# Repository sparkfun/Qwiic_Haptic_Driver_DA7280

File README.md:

SparkFun Qwiic Haptic Driver - DA7280
========================================

<table class="table table-hover table-striped table-bordered">
  <tr align="center">
   <td></td>
   <td></td>
  </tr>
  <tr align="center">
   <td><i>SparkFun Qwiic Haptic Driver - DA7280 [<a href="https://www.sparkfun.com/products/17590">ROB-17590</a>]</i></td>
   <td><i>SparkFun Qwiic Haptic Driver Kit - DA7280 [<a href="https://www.sparkfun.com/products/18247">ROB-18247</a>]</i></td>
  </tr>
</table>

The SparkFun Qwiic Haptic Driver includes an itty-bitty, Linear Resonant Actuator (LRA) vibration motor and Dialog Semiconductor's DA7280 motor driver IC for applications that require haptic feedback. The kit is intended for applications where the vibration motor needs to be mounted separately from the board. Please be aware that you will need to manually solder the wires and motor to the board.

Control the vibration motor with the DA7280 via I<sup>2</sup>C, PWM, or a combination of three general purpose input pins. Utilizing our handy Qwiic system, no soldering is required to connect it to the rest of your system. However, we still include 0.1"-spaced PTH pads in case you prefer to use a breadboard to access the driver's I<sup>2</sup>C, power, interrupt, and general purpose input pins on the edge of the board.

This board is great for projects that require a physical indicator whenever an event is triggered. Add it to your remote control to notify you when your robot has hit a wall. Combine it with an accelerometer to remind you to correct your posture. Or use it with a distance sensor to alert you when a ninja is walking up to you at your desk.

Repository Contents
-------------------

* **/Documentation** - Data sheets, additional product information
* **/Hardware** - Eagle design files (.brd, .sch)
* **/Production** - Production panel files (.brd)

Documentation
--------------

* **[Library](https://github.com/sparkfun/DA7280_Haptic_Driver_Arduino_Library)** - Arduino library
* **[Hookup Guide](https://learn.sparkfun.com/tutorials/1461)**

Product Versions
----------------

* [ROB-17590](https://www.sparkfun.com/products/17590)

Version History
---------------

* v1.0 - Initial Release

License Information
-------------------

This product is _**open source**_! 

Please review the LICENSE.md file for license information. 

If you have any questions or concerns on licensing, please contact technical support on our [SparkFun forums](https://forum.sparkfun.com/viewforum.php?f=152).

Distributed as-is; no warranty is given.

- Your friends at SparkFun.

_<COLLABORATION CREDIT>_

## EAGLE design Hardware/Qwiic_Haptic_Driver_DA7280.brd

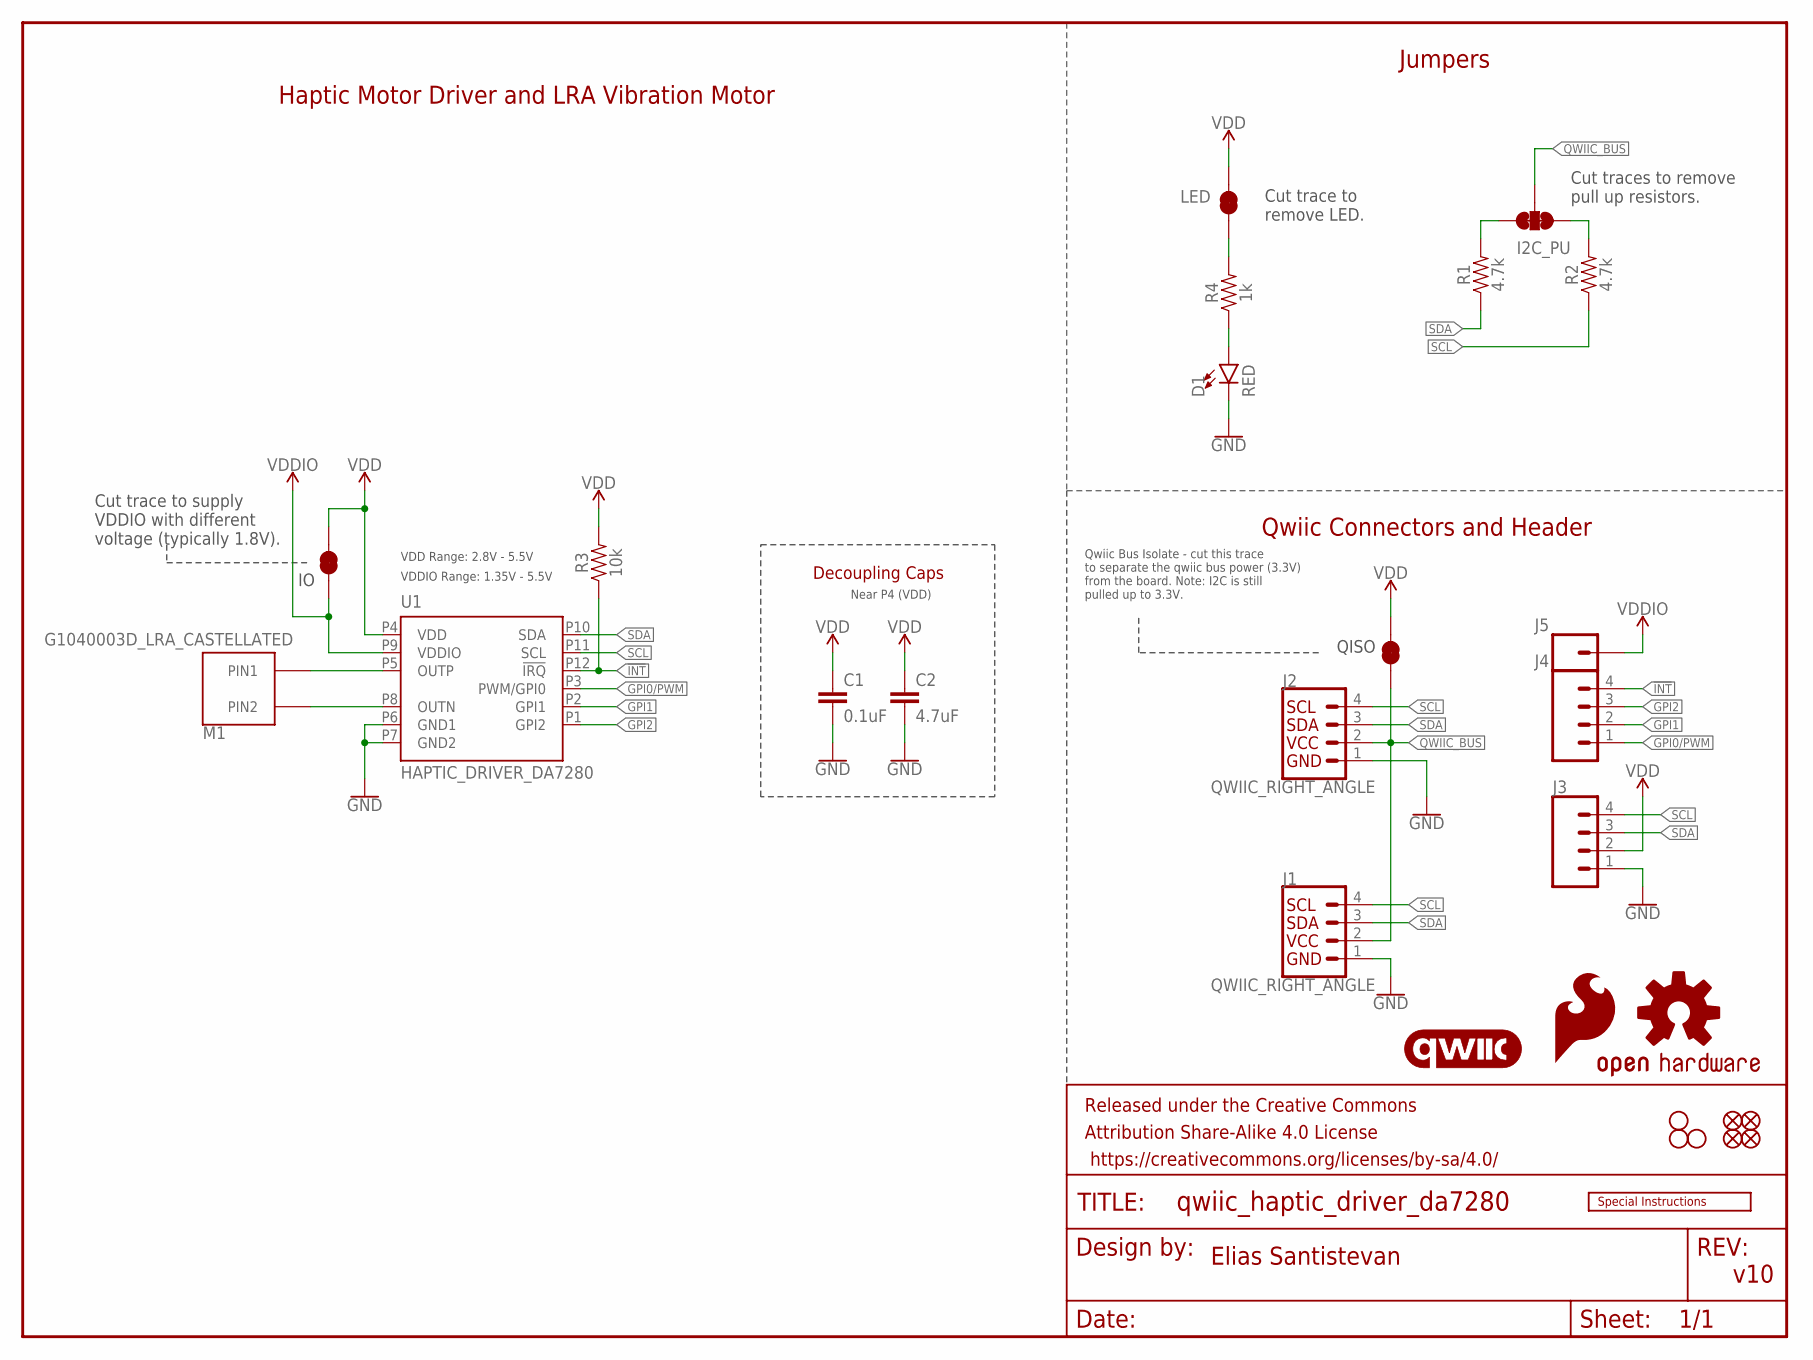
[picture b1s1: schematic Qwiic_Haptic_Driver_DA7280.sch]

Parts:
C1: 0.1uF; 0603
C2: 4.7uF; 0603
D1: RED; LED-0603
FD1, FD2, FD3, FD4: FIDUCIALUFIDUCIAL; FIDUCIAL-MICRO
FRAME1: FRAME-LETTER; CREATIVE_COMMONS
H1, H2, H4: STAND-OFFTIGHT; STAND-OFF-TIGHT
J1, J2: QWIIC_RIGHT_ANGLE; JST04_1MM_RA
J3, J4: CONN_041X04_NO_SILK_NO_POP; 1X04_NO_SILK
J5: CONN_01PTH_NO_SILK_YES_STOP; 1X01_NO_SILK
JP1, JP2, JP4: LED; SMT-JUMPER_2_NC_TRACE_SILK
JP3: I2C_PU; SMT-JUMPER_3_2-NC_TRACE_SILK
LOGO1: SPECIAL_INSTRUCTIONS-ORDERING; ORDERING_INSTRUCTIONS
LOGO2: OSHW-LOGOS; OSHW-LOGO-S
LOGO4: SFE_LOGO_FLAME.1_INCH; SFE_LOGO_FLAME_.1
M1: G1040003D_LRA_CASTELLATED; COIN_VIBRATION_MOTOR_CASTEL
R1, R2: 4.7k; 0603
R3: 10k; 0603
R4: 1k; 0603
U1: HAPTIC_DRIVER_DA7280; QFN_DA7280
U$1: QWIIC_LOGO_3MM; QWIIC_3MM

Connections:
!INT!: J4.4, R3.1, U1.P12 (!IRQ!)
GND: C1.2, C2.2, D1.C, J1.1, J2.1, J3.1, U1.P6 (GND1), U1.P7 (GND2)
GPI0/PWM: J4.1, U1.P3 (PWM/GPI0)
GPI1: J4.2, U1.P2 (GPI1)
GPI2: J4.3, U1.P1 (GPI2)
unnamed: D1.A, R4.1
unnamed: JP1.1, R4.2
unnamed: JP3.3, R1.2
unnamed: JP3.1, R2.2
unnamed: M1.P$1 (PIN1), U1.P5 (OUTP)
unnamed: M1.P$2 (PIN2), U1.P8 (OUTN)
QWIIC_BUS: J1.2, J2.2, JP3.2, JP4.1
SCL: J1.4, J2.4, J3.4, R2.1, U1.P11 (SCL)
SDA: J1.3, J2.3, J3.3, R1.1, U1.P10 (SDA)
VDD: C1.1, C2.1, J3.2, JP1.2, JP2.2, JP4.2, R3.2, U1.P4 (VDD)
VDDIO: J5.1, JP2.1, U1.P9 (VDDIO)

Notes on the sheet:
v10
Qwiic Connectors and Header
Jumpers
Cut trace to remove LED.
Cut traces to remove pull up resistors.
Haptic Motor Driver and LRA Vibration Motor
Elias Santistevan
Near P4 (VDD)
Decoupling Caps
VDD Range: 2.8V - 5.5V
VDDIO Range: 1.35V - 5.5V
Cut trace to supply VDDIO with different voltage (typically 1.8V).
QISO
Qwiic Bus Isolate - cut this trace to separate the qwiic bus power (3.3V) from the board. Note: I2C is still pulled up to 3.3V.

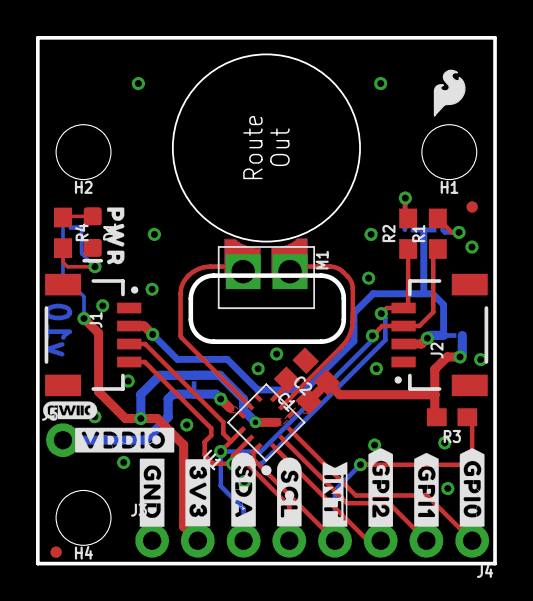
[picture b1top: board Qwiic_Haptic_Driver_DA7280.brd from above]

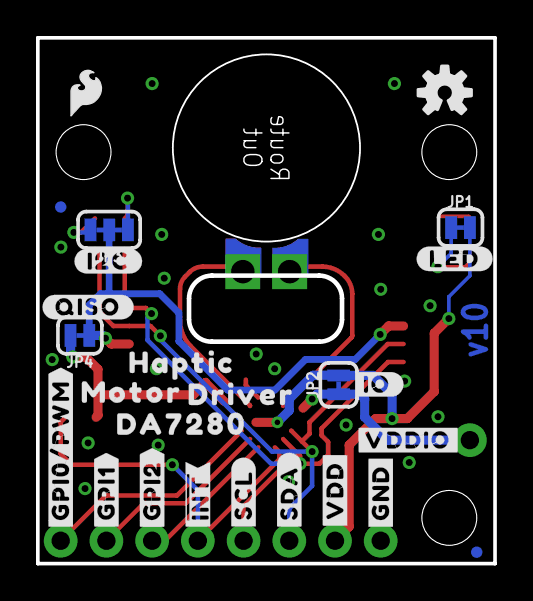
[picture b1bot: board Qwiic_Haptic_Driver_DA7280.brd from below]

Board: 2 copper layers, 25.3 x 29.2 mm, 58 parts (25 on the bottom side), 16 nets.

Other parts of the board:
U$2: #3V3#1
U$3, U$18: #GND#0
U$4: #GPI0#6
U$5: #GPI1#6
U$6: #GPI2#6
U$7: #VDD#4
U$8: #SDA#4
U$9: HAPTIC6
U$10: MOTOR7
U$11: DRIVER8
U$12: #GPI0#PWM#2
U$13: #GPI1#2
U$14: #GPI2#2
U$15, U$25: #VDDIO#5
U$16: #SDA#0
U$19: #SCL#5
U$20: PWR72810
U$21: #SCL#1
U$23: #I2C#4
U$24: #LED#4
U$26: SFE_LOGO_FLAME_.1
U$27: ##INT##3
U$28: ##INT##6
U$29: DA72809
U$30: #IO#6
U$31: #QISO#0

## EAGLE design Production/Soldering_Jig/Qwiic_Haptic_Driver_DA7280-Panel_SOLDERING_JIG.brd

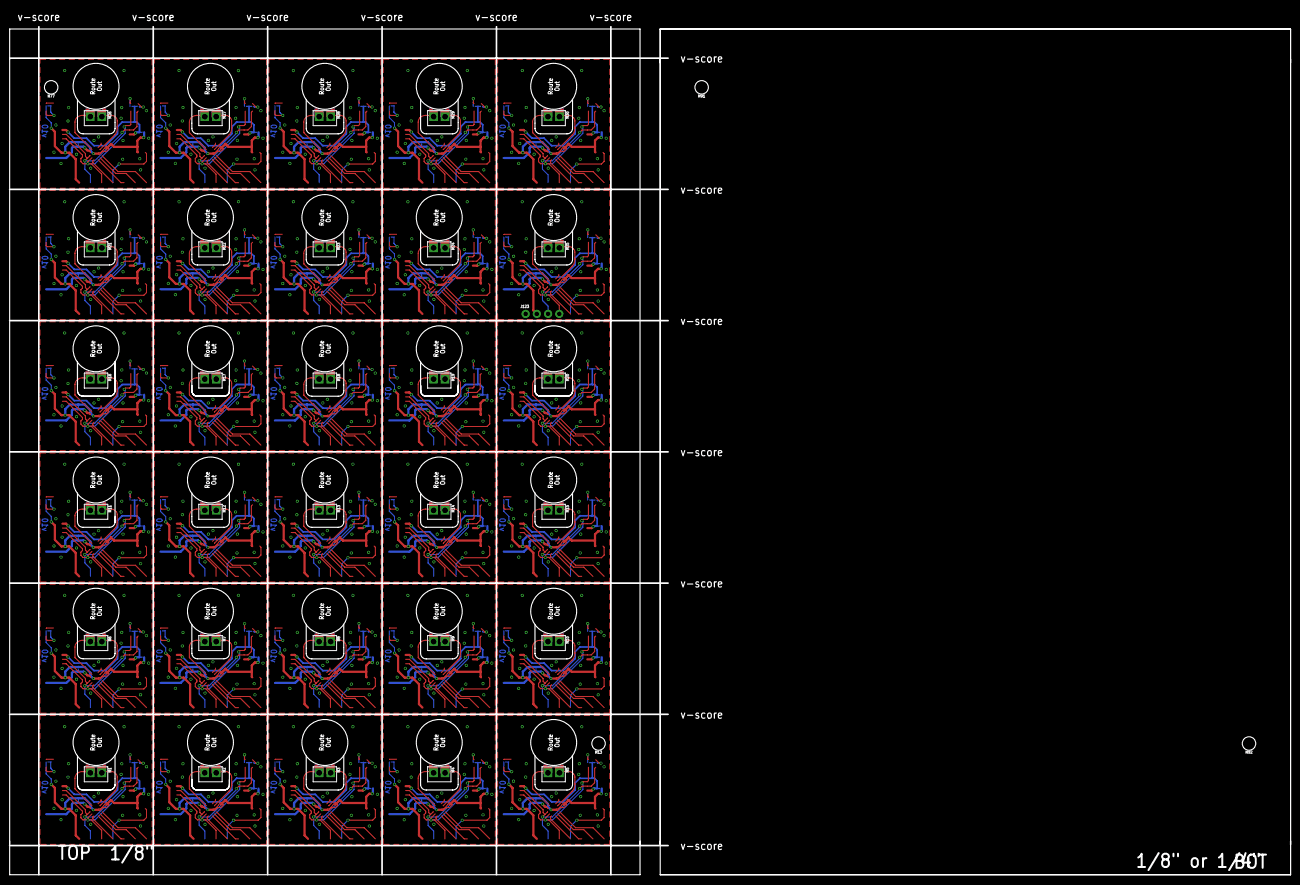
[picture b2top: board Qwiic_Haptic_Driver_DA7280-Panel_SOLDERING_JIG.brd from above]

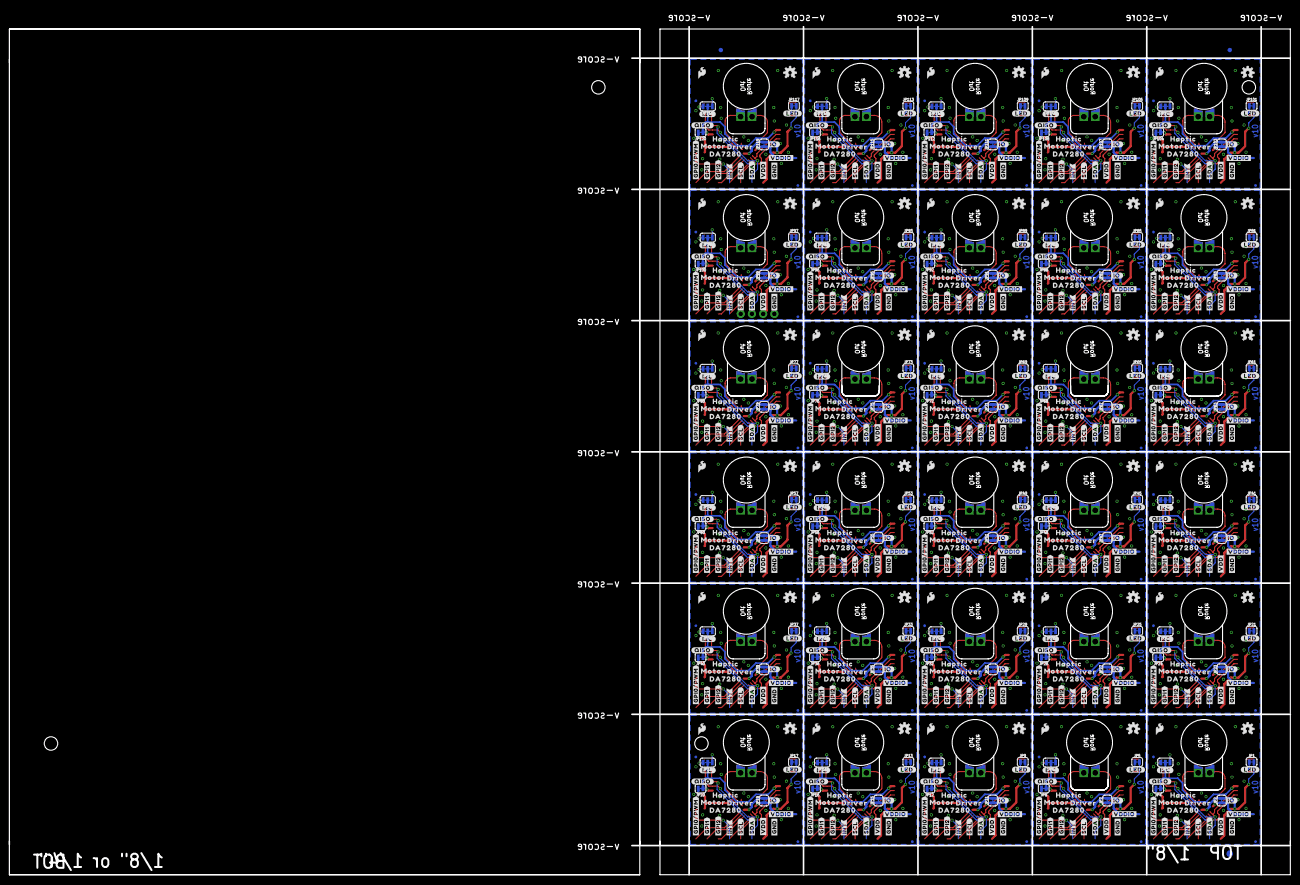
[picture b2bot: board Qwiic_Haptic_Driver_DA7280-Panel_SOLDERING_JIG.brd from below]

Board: 2 copper layers, 290.0 x 196.0 mm, 788 parts (753 on the bottom side), 60 nets.

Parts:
E$2, E$4: FIDUCIAL-1X2
E$6: FIDUCIAL-1.5X3
FD2, FD4, FD6, FD8, FD10, FD12, FD14, FD16, FD18, FD20, FD22, FD24, FD26, FD28, FD30, FD32, FD34, FD36, FD38, FD40, FD42, FD44, FD46, FD48, FD50, FD52, FD54, FD56, FD58, FD60, FD62, FD64, FD66, FD68, FD70, FD72, FD74, FD76, FD78, FD80, FD82, FD84, FD86, FD88, FD90, FD92, FD94, FD96, FD98, FD100, FD102, FD104, FD106, FD108, FD110, FD112, FD114, FD116, FD118, FD120: FIDUCIALUFIDUCIAL; FIDUCIAL-MICRO
H13, H77, H91, H92: STAND-OFFTIGHT; STAND-OFF-TIGHT
J123: 1X04_NO_SILK
JP1, JP2, JP4, JP5, JP7, JP8, JP9, JP11, JP12, JP13, JP15, JP16, JP17, JP19, JP20, JP21, JP23, JP24, JP25, JP27, JP28, JP29, JP31, JP32, JP33, JP35, JP36, JP37, JP39, JP40, JP41, JP43, JP44, JP45, JP47, JP48, JP49, JP51, JP52, JP53, JP55, JP56, JP57, JP59, JP60, JP61, JP63, JP64, JP65, JP67, JP68, JP69, JP71, JP72, JP73, JP75, JP76, JP77, JP79, JP80, JP81, JP83, JP84, JP85, JP87, JP88, JP89, JP91, JP92, JP93, JP95, JP96, JP97, JP99, JP100, JP101, JP103, JP104, JP105, JP107, JP108, JP109, JP111, JP112, JP113, JP115, JP116, JP117, JP119, JP120: LED; SMT-JUMPER_2_NC_TRACE_SILK
JP3, JP6, JP10, JP14, JP18, JP22, JP26, JP30, JP34, JP38, JP42, JP46, JP50, JP54, JP58, JP62, JP66, JP70, JP74, JP78, JP82, JP86, JP90, JP94, JP98, JP102, JP106, JP110, JP114, JP118: I2C_PU; SMT-JUMPER_3_2-NC_TRACE_SILK
LOGO1, LOGO2, LOGO5, LOGO7, LOGO9, LOGO11, LOGO13, LOGO15, LOGO17, LOGO19, LOGO21, LOGO23, LOGO25, LOGO27, LOGO29, LOGO31, LOGO33, LOGO35, LOGO37, LOGO39, LOGO41, LOGO43, LOGO45, LOGO47, LOGO49, LOGO51, LOGO53, LOGO55, LOGO57, LOGO59: OSHW-LOGOS; OSHW-LOGO-S
M1, M2, M3, M4, M5, M6, M7, M8, M9, M10, M11, M12, M13, M14, M15, M16, M17, M18, M19, M20, M21, M22, M23, M24, M25, M26, M27, M28, M29, M30: G1040003D_LRA_CASTELLATED; COIN_VIBRATION_MOTOR_CASTEL
U$7, U$50, U$79, U$108, U$137, U$166, U$195, U$224, U$253, U$282, U$311, U$340, U$369, U$398, U$427, U$456, U$485, U$514, U$543, U$572, U$601, U$630, U$659, U$688, U$717, U$746, U$775, U$804, U$833, U$862: #VDD#4
U$9, U$53, U$82, U$111, U$140, U$169, U$198, U$227, U$256, U$285, U$314, U$343, U$372, U$401, U$430, U$459, U$488, U$517, U$546, U$575, U$604, U$633, U$662, U$691, U$720, U$749, U$778, U$807, U$836, U$865: HAPTIC6
U$10, U$54, U$83, U$112, U$141, U$170, U$199, U$228, U$257, U$286, U$315, U$344, U$373, U$402, U$431, U$460, U$489, U$518, U$547, U$576, U$605, U$634, U$663, U$692, U$721, U$750, U$779, U$808, U$837, U$866: MOTOR7
U$11, U$55, U$84, U$113, U$142, U$171, U$200, U$229, U$258, U$287, U$316, U$345, U$374, U$403, U$432, U$461, U$490, U$519, U$548, U$577, U$606, U$635, U$664, U$693, U$722, U$751, U$780, U$809, U$838, U$867: DRIVER8
U$12, U$36, U$65, U$94, U$123, U$152, U$181, U$210, U$239, U$268, U$297, U$326, U$355, U$384, U$413, U$442, U$471, U$500, U$529, U$558, U$587, U$616, U$645, U$674, U$703, U$732, U$761, U$790, U$819, U$848: #GPI0#PWM#2
U$13, U$37, U$66, U$95, U$124, U$153, U$182, U$211, U$240, U$269, U$298, U$327, U$356, U$385, U$414, U$443, U$472, U$501, U$530, U$559, U$588, U$617, U$646, U$675, U$704, U$733, U$762, U$791, U$820, U$849: #GPI1#2
U$14, U$38, U$67, U$96, U$125, U$154, U$183, U$212, U$241, U$270, U$299, U$328, U$357, U$386, U$415, U$444, U$473, U$502, U$531, U$560, U$589, U$618, U$647, U$676, U$705, U$734, U$763, U$792, U$821, U$850: #GPI2#2
U$16, U$39, U$68, U$97, U$126, U$155, U$184, U$213, U$242, U$271, U$300, U$329, U$358, U$387, U$416, U$445, U$474, U$503, U$532, U$561, U$590, U$619, U$648, U$677, U$706, U$735, U$764, U$793, U$822, U$851: #SDA#0
U$18, U$40, U$69, U$98, U$127, U$156, U$185, U$214, U$243, U$272, U$301, U$330, U$359, U$388, U$417, U$446, U$475, U$504, U$533, U$562, U$591, U$620, U$649, U$678, U$707, U$736, U$765, U$794, U$823, U$852: #GND#0
U$21, U$43, U$72, U$101, U$130, U$159, U$188, U$217, U$246, U$275, U$304, U$333, U$362, U$391, U$420, U$449, U$478, U$507, U$536, U$565, U$594, U$623, U$652, U$681, U$710, U$739, U$768, U$797, U$826, U$855: #SCL#1
U$23, U$44, U$73, U$102, U$131, U$160, U$189, U$218, U$247, U$276, U$305, U$334, U$363, U$392, U$421, U$450, U$479, U$508, U$537, U$566, U$595, U$624, U$653, U$682, U$711, U$740, U$769, U$798, U$827, U$856: #I2C#4
U$24, U$45, U$74, U$103, U$132, U$161, U$190, U$219, U$248, U$277, U$306, U$335, U$364, U$393, U$422, U$451, U$480, U$509, U$538, U$567, U$596, U$625, U$654, U$683, U$712, U$741, U$770, U$799, U$828, U$857: #LED#4
U$25, U$52, U$81, U$110, U$139, U$168, U$197, U$226, U$255, U$284, U$313, U$342, U$371, U$400, U$429, U$458, U$487, U$516, U$545, U$574, U$603, U$632, U$661, U$690, U$719, U$748, U$777, U$806, U$835, U$864: #VDDIO#5
U$26, U$47, U$76, U$105, U$134, U$163, U$192, U$221, U$250, U$279, U$308, U$337, U$366, U$395, U$424, U$453, U$482, U$511, U$540, U$569, U$598, U$627, U$656, U$685, U$714, U$743, U$772, U$801, U$830, U$859: SFE_LOGO_FLAME_.1
U$27, U$48, U$77, U$106, U$135, U$164, U$193, U$222, U$251, U$280, U$309, U$338, U$367, U$396, U$425, U$454, U$483, U$512, U$541, U$570, U$599, U$628, U$657, U$686, U$715, U$744, U$773, U$802, U$831, U$860: ##INT##3
U$29, U$56, U$85, U$114, U$143, U$172, U$201, U$230, U$259, U$288, U$317, U$346, U$375, U$404, U$433, U$462, U$491, U$520, U$549, U$578, U$607, U$636, U$665, U$694, U$723, U$752, U$781, U$810, U$839, U$868: DA72809
U$30, U$57, U$86, U$115, U$144, U$173, U$202, U$231, U$260, U$289, U$318, U$347, U$376, U$405, U$434, U$463, U$492, U$521, U$550, U$579, U$608, U$637, U$666, U$695, U$724, U$753, U$782, U$811, U$840, U$869: #IO#6
U$31, U$58, U$87, U$116, U$145, U$174, U$203, U$232, U$261, U$290, U$319, U$348, U$377, U$406, U$435, U$464, U$493, U$522, U$551, U$580, U$609, U$638, U$667, U$696, U$725, U$754, U$783, U$812, U$841, U$870: #QISO#0

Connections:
QWIIC_BUS: JP3.2, JP4.1
QWIIC_BUS1: JP6.2, JP8.1
QWIIC_BUS2: JP10.2, JP12.1
QWIIC_BUS3: JP14.2, JP16.1
QWIIC_BUS4: JP18.2, JP20.1
QWIIC_BUS5: JP22.2, JP24.1
QWIIC_BUS6: JP26.2, JP28.1
QWIIC_BUS7: JP30.2, JP32.1
QWIIC_BUS8: JP34.2, JP36.1
QWIIC_BUS9: JP38.2, JP40.1
QWIIC_BUS10: JP42.2, JP44.1
QWIIC_BUS11: JP46.2, JP48.1
QWIIC_BUS12: JP50.2, JP52.1
QWIIC_BUS13: JP54.2, JP56.1
QWIIC_BUS14: JP58.2, JP60.1
QWIIC_BUS15: JP62.2, JP64.1
QWIIC_BUS16: JP66.2, JP68.1
QWIIC_BUS17: JP70.2, JP72.1
QWIIC_BUS18: JP74.2, JP76.1
QWIIC_BUS19: JP78.2, JP80.1
QWIIC_BUS20: JP82.2, JP84.1
QWIIC_BUS21: JP86.2, JP88.1
QWIIC_BUS22: JP90.2, JP92.1
QWIIC_BUS23: JP94.2, JP96.1
QWIIC_BUS24: JP98.2, JP100.1
QWIIC_BUS25: JP102.2, JP104.1
QWIIC_BUS26: JP106.2, JP108.1
QWIIC_BUS27: JP110.2, JP112.1
QWIIC_BUS28: JP114.2, JP116.1
QWIIC_BUS29: JP118.2, JP120.1
VDD: JP1.2, JP2.2, JP4.2
VDD1: JP5.2, JP7.2, JP8.2
VDD2: JP9.2, JP11.2, JP12.2
VDD3: JP13.2, JP15.2, JP16.2
VDD4: JP17.2, JP19.2, JP20.2
VDD5: JP21.2, JP23.2, JP24.2
VDD6: JP25.2, JP27.2, JP28.2
VDD7: JP29.2, JP31.2, JP32.2
VDD8: JP33.2, JP35.2, JP36.2
VDD9: JP37.2, JP39.2, JP40.2
VDD10: JP41.2, JP43.2, JP44.2
VDD11: JP45.2, JP47.2, JP48.2
VDD12: JP49.2, JP51.2, JP52.2
VDD13: JP53.2, JP55.2, JP56.2
VDD14: JP57.2, JP59.2, JP60.2
VDD15: JP61.2, JP63.2, JP64.2
VDD16: JP65.2, JP67.2, JP68.2
VDD17: JP69.2, JP71.2, JP72.2
VDD18: JP73.2, JP75.2, JP76.2
VDD19: JP77.2, JP79.2, JP80.2
VDD20: JP81.2, JP83.2, JP84.2
VDD21: JP85.2, JP87.2, JP88.2
VDD22: JP89.2, JP91.2, JP92.2
VDD23: JP93.2, JP95.2, JP96.2
VDD24: J123.2, JP97.2, JP99.2, JP100.2
VDD25: JP101.2, JP103.2, JP104.2
VDD26: JP105.2, JP107.2, JP108.2
VDD27: JP109.2, JP111.2, JP112.2
VDD28: JP113.2, JP115.2, JP116.2
VDD29: JP117.2, JP119.2, JP120.2

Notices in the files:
parts and their libraries:
SparkFun-LED: Licensing: Creative Commons ShareAlike 4.0 International - https://creativecommons.org/licenses/by-sa/4.0
SparkFun-Aesthetics: Released under the Creative Commons Attribution Share-Alike 4.0 License
SparkFun-Aesthetics: https://creativecommons.org/licenses/by-sa/4.0
